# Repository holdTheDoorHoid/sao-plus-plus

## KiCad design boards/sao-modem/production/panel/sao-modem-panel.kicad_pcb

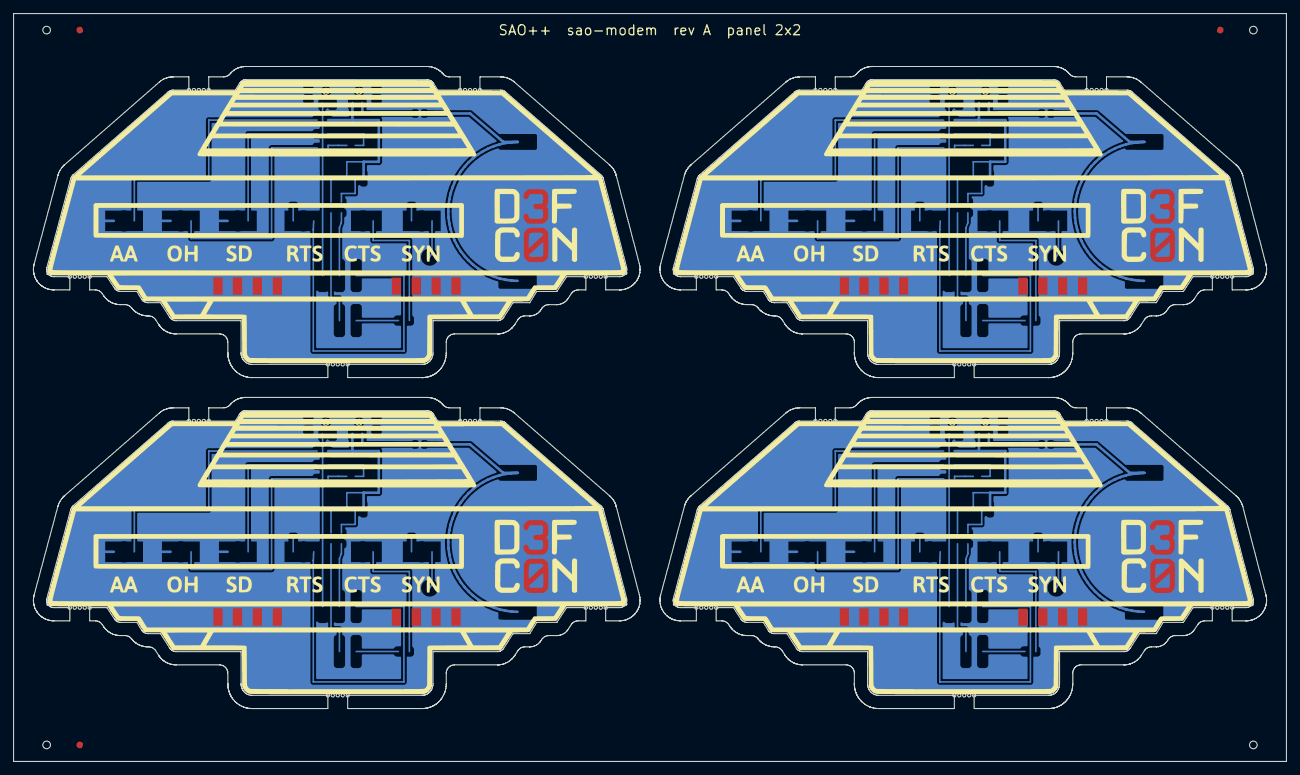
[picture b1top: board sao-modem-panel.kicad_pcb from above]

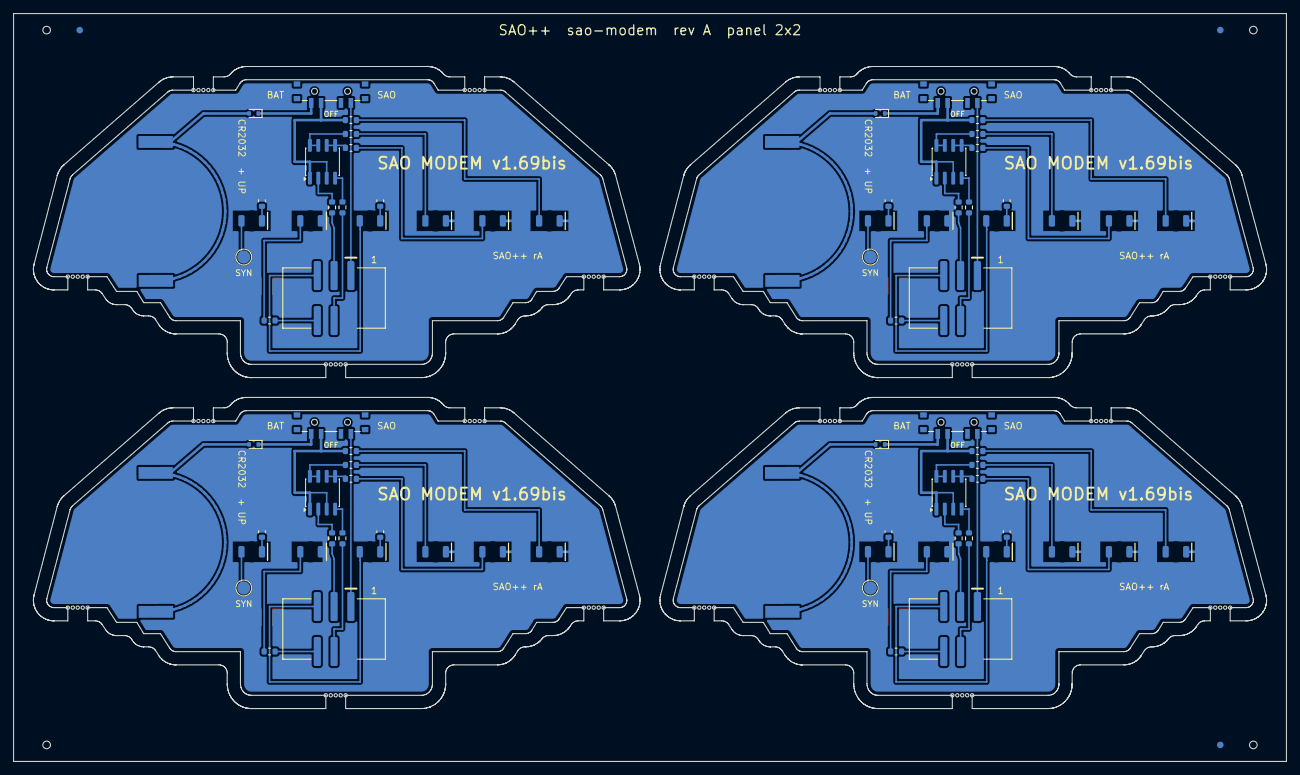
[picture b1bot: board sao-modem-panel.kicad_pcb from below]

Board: 2 copper layers, 192.4 x 113.1 mm, 80 parts (80 on the bottom side), 80 nets.

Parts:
BT101, BT201, BT301, BT401: CR2032; SAOPP_BAT-01_CR2032_SMD_TE_BAT-HLD-001
D101, D102, D103, D104, D105, D106, D201, D202, D203, D204, D205, D206, D301, D302, D303, D304, D305, D306, D401, D402, D403, D404, D405, D406: red; SAOPP_LED-10_1206_ReverseMount_ThroughBoard
D107, D207, D307, D407: RB751S40; D_SOD-523
J101, J201, J301, J401: SAO v1.69bis; SAOPP_CONN-01_BoxHeader_2x03_P2.54mm_SMD_XFCN_BH254VS-6P
Q101, Q201, Q301, Q401: DMP3085LSD; SOIC-8_3.9x4.9mm_P1.27mm
R101, R102, R103, R104, R105, R106, R201, R202, R203, R204, R205, R206, R301, R302, R303, R304, R305, R306, R401, R402, R403, R404, R405, R406: 1.3k; SAOPP_R_0603_1608Metric
R107, R207, R307, R407: 4.7k; R_0603_1608Metric
R108, R208, R308, R408: 10k; R_0603_1608Metric
SW101, SW201, SW301, SW401: SAO / OFF / BAT; SAOPP_SW-01_Slide_SP3T_CK_PCM13SMTR
TP1, TP1#2, TP1#3, TP1#4: SYN pad; TestPoint_Pad_D2.0mm

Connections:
AA_A: D101.2, R101.2
B2-AA_A: D201.2, R201.2
B2-CTS_A: D205.2, R205.1
B2-GND: BT201.2, D201.1, D202.1, D203.1, D205.1, J201.2, R204.2, R206.2
B2-GPIO1: D204.2, J201.5
B2-GPIO2: J201.6, R205.2
B2-G_SCL: Q201.4, R207.2
B2-G_SDA: Q201.2, R208.2
B2-OH_A: D202.2, R202.2
B2-Q_OH: Q201.5, Q201.6, R202.1
B2-Q_SD: Q201.7, Q201.8, R203.1
B2-RTS_K: D204.1, R204.1
B2-SCL: J201.4, R207.1
B2-SDA: J201.3, R208.1
B2-SD_A: D203.2, R203.2
B2-SYN: D206.2, TP1#3.1
B2-SYN_K: D206.1, R206.1
B2-VBAT: BT201.1, D207.2
B2-VCELL: D207.1, SW201.4
B2-VLOAD: Q201.1, Q201.3, R201.1, SW201.3
B2-VSAO: J201.1, SW201.1
B3-AA_A: D301.2, R301.2
B3-CTS_A: D305.2, R305.1
B3-GND: BT301.2, D301.1, D302.1, D303.1, D305.1, J301.2, R304.2, R306.2
B3-GPIO1: D304.2, J301.5
B3-GPIO2: J301.6, R305.2
B3-G_SCL: Q301.4, R307.2
B3-G_SDA: Q301.2, R308.2
B3-OH_A: D302.2, R302.2
B3-Q_OH: Q301.5, Q301.6, R302.1
B3-Q_SD: Q301.7, Q301.8, R303.1
B3-RTS_K: D304.1, R304.1
B3-SCL: J301.4, R307.1
B3-SDA: J301.3, R308.1
B3-SD_A: D303.2, R303.2
B3-SYN: D306.2, TP1#2.1
B3-SYN_K: D306.1, R306.1
B3-VBAT: BT301.1, D307.2
B3-VCELL: D307.1, SW301.4
B3-VLOAD: Q301.1, Q301.3, R301.1, SW301.3
B3-VSAO: J301.1, SW301.1
B4-AA_A: D401.2, R401.2
B4-CTS_A: D405.2, R405.1
B4-GND: BT401.2, D401.1, D402.1, D403.1, D405.1, J401.2, R404.2, R406.2
B4-GPIO1: D404.2, J401.5
B4-GPIO2: J401.6, R405.2
B4-G_SCL: Q401.4, R407.2
B4-G_SDA: Q401.2, R408.2
B4-OH_A: D402.2, R402.2
B4-Q_OH: Q401.5, Q401.6, R402.1
B4-Q_SD: Q401.7, Q401.8, R403.1
B4-RTS_K: D404.1, R404.1
B4-SCL: J401.4, R407.1
B4-SDA: J401.3, R408.1
B4-SD_A: D403.2, R403.2
B4-SYN: D406.2, TP1#4.1
B4-SYN_K: D406.1, R406.1
B4-VBAT: BT401.1, D407.2
B4-VCELL: D407.1, SW401.4
B4-VLOAD: Q401.1, Q401.3, R401.1, SW401.3
B4-VSAO: J401.1, SW401.1
CTS_A: D105.2, R105.1
GND: BT101.2, D101.1, D102.1, D103.1, D105.1, J101.2, R104.2, R106.2
GPIO1: D104.2, J101.5
GPIO2: J101.6, R105.2
G_SCL: Q101.4, R107.2
G_SDA: Q101.2, R108.2
OH_A: D102.2, R102.2
Q_OH: Q101.5, Q101.6, R102.1
Q_SD: Q101.7, Q101.8, R103.1
RTS_K: D104.1, R104.1
SCL: J101.4, R107.1
SDA: J101.3, R108.1
SD_A: D103.2, R103.2
SYN: D106.2, TP1.1
SYN_K: D106.1, R106.1
VBAT: BT101.1, D107.2
VCELL: D107.1, SW101.4
VLOAD: Q101.1, Q101.3, R101.1, SW101.3
VSAO: J101.1, SW101.1

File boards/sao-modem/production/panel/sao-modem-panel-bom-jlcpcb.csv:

Comment,Designator,Footprint,LCSC Part #
CR2032,"BT101,BT201,BT301,BT401",SAOPP_BAT-01_CR2032_SMD_TE_BAT-HLD-001,C7501066
red,"D101,D102,D103,D104,D105,D106,D201,D202,D203,D204,D205,D206,D301,D302,D303,D304,D305,D306,D401,D402,D403,D404,D405,D406",SAOPP_LED-10_1206_ReverseMount_ThroughBoard,C125107
RB751S40,"D107,D207,D307,D407",D_SOD-523,C232576
SAO v1.69bis,"J101,J201,J301,J401",SAOPP_CONN-01_BoxHeader_2x03_P2.54mm_SMD_XFCN_BH254VS-6P,C492445
DMP3085LSD,"Q101,Q201,Q301,Q401",SOIC-8_3.9x4.9mm_P1.27mm,
1.3k,"R101,R102,R103,R104,R105,R106,R201,R202,R203,R204,R205,R206,R301,R302,R303,R304,R305,R306,R401,R402,R403,R404,R405,R406",SAOPP_R_0603_1608Metric,C22767
4.7k,"R107,R207,R307,R407",R_0603_1608Metric,
10k,"R108,R208,R308,R408",R_0603_1608Metric,
SAO / OFF / BAT,"SW101,SW201,SW301,SW401",SAOPP_SW-01_Slide_SP3T_CK_PCM13SMTR,C221842

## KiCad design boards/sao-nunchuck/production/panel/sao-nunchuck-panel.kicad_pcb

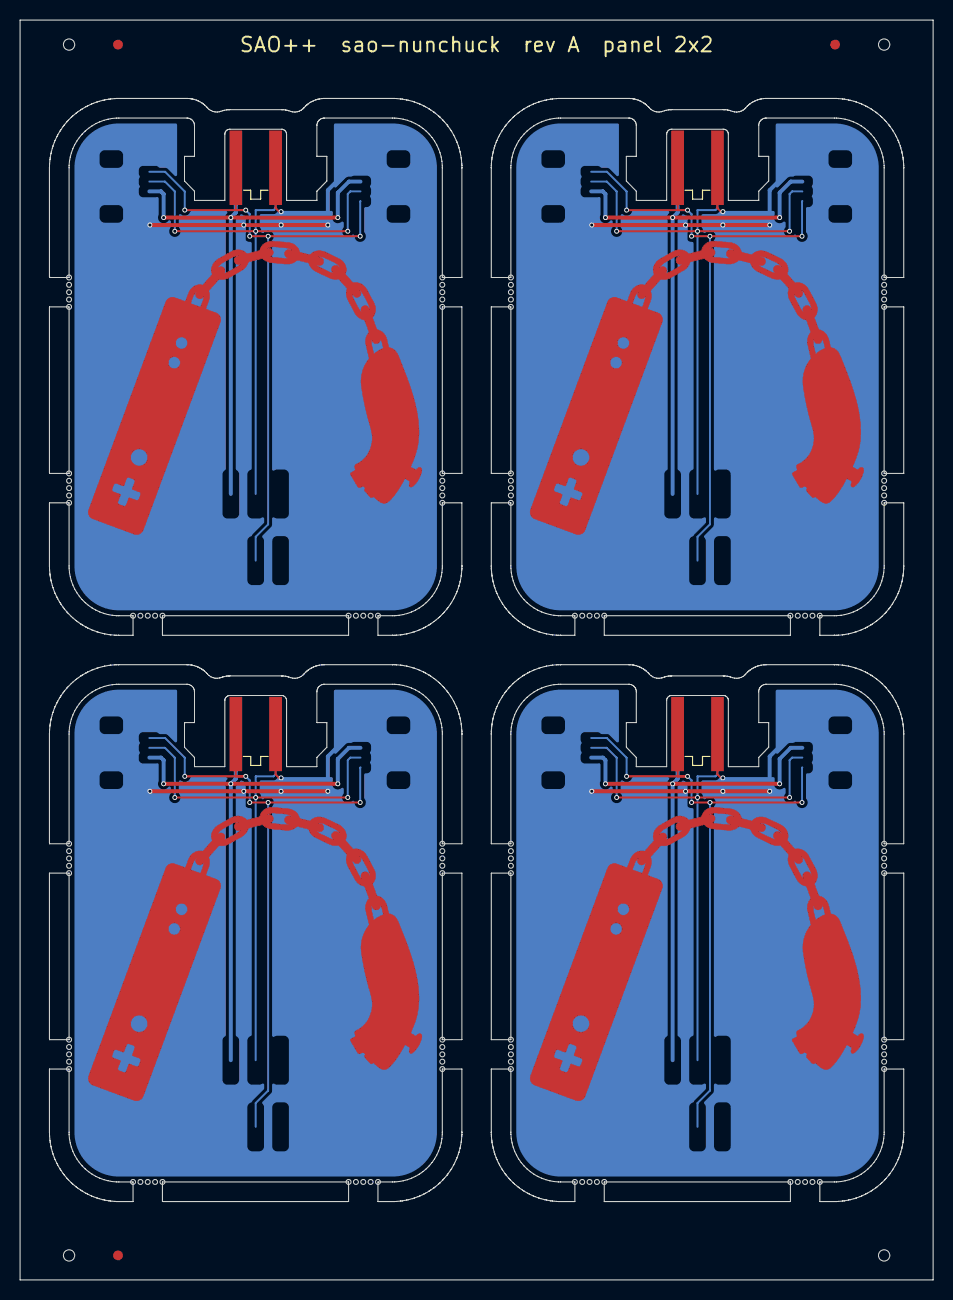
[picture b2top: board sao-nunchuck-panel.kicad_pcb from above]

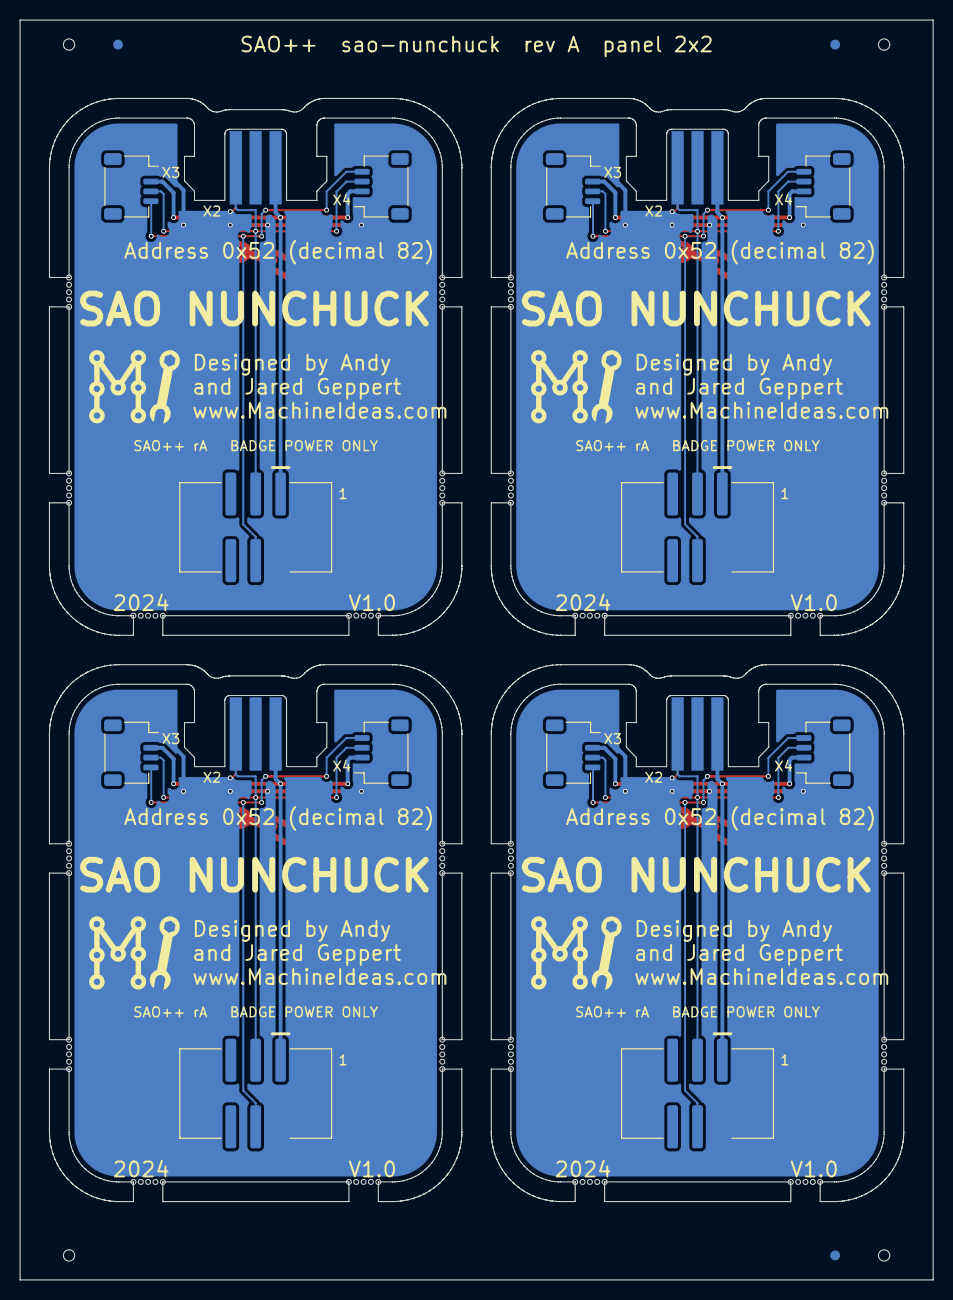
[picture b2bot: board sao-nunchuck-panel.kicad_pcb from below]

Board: 2 copper layers, 93.2 x 128.6 mm, 20 parts (16 on the bottom side), 16 nets.

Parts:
J101, J201, J301, J401: SAO v1.69bis; SAOPP_CONN-01_BoxHeader_2x03_P2.54mm_SMD_XFCN_BH254VS-6P
L1, L1#2, L1#3, L1#4: Machine_Ideas_logo
X102, X202, X302, X402: Nunchuck plug (board edge fingers); Nunchuck_Plug_EdgeFingers
X103, X104, X203, X204, X303, X304, X403, X404: Qwiic (pads only, not fitted); Qwiic_JST_SH_SM04B-SRSS-TB_NotFitted

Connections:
3V3: J101.1, X102.3, X103.2, X104.2
B2-3V3: J201.1, X202.3, X203.2, X204.2
B2-GND: J201.2, X202.6, X203.1, X204.1
B2-SCL: J201.4, X202.4, X203.4, X204.4
B2-SDA: J201.3, X202.1, X203.3, X204.3
B3-3V3: J301.1, X302.3, X303.2, X304.2
B3-GND: J301.2, X302.6, X303.1, X304.1
B3-SCL: J301.4, X302.4, X303.4, X304.4
B3-SDA: J301.3, X302.1, X303.3, X304.3
B4-3V3: J401.1, X402.3, X403.2, X404.2
B4-GND: J401.2, X402.6, X403.1, X404.1
B4-SCL: J401.4, X402.4, X403.4, X404.4
B4-SDA: J401.3, X402.1, X403.3, X404.3
GND: J101.2, X102.6, X103.1, X104.1
SCL: J101.4, X102.4, X103.4, X104.4
SDA: J101.3, X102.1, X103.3, X104.3

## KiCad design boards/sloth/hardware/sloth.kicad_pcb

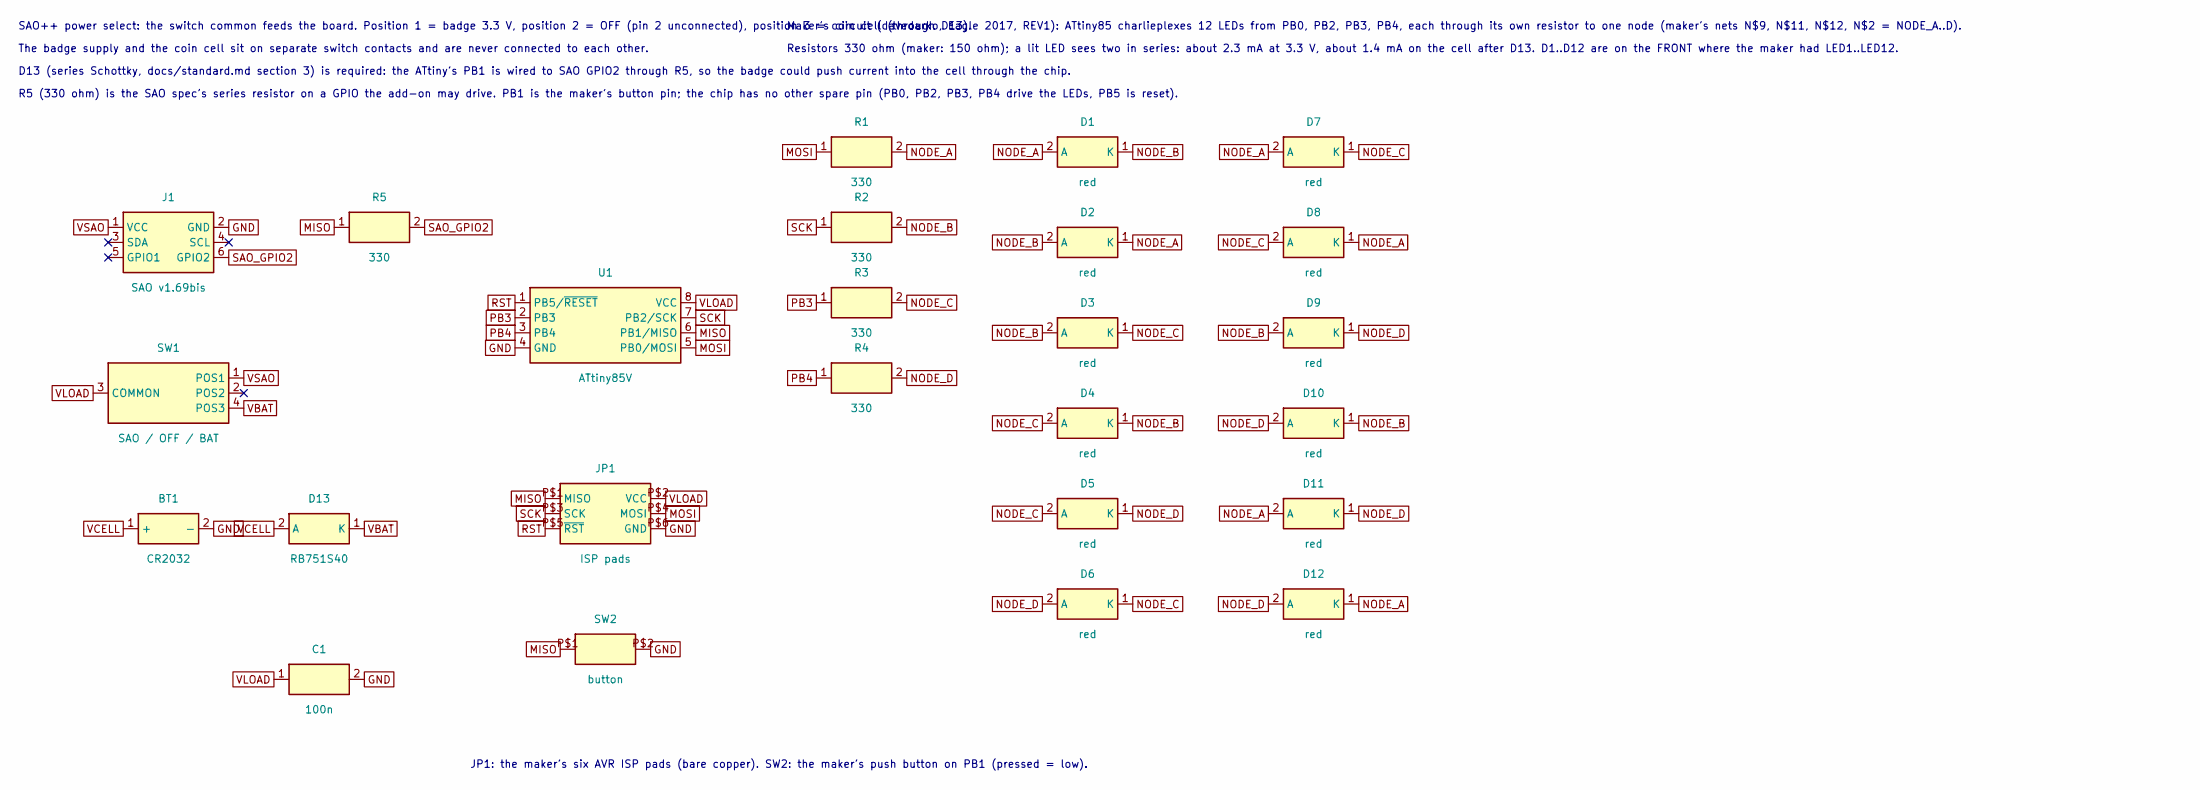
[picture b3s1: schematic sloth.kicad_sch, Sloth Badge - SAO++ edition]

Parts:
BT1: CR2032; SAOPP_BAT-01_CR2032_SMD_TE_BAT-HLD-001; MPN BAT-HLD-001; LCSC C7501066
C1: 100n; SAOPP_C_0603_1608Metric; MPN CC0603KRX7R9BB104; LCSC C14663
D1, D2, D3, D4, D5, D6, D7, D8, D9, D10, D11, D12: red; LED_0603_1608Metric_Pad1.05x0.95mm_HandSolder; MPN LTST-C191KRKT; LCSC C125099
D13: RB751S40; D_SOD-523; MPN RB751S40T1G; LCSC C232576
J1: SAO v1.69bis; SAOPP_CONN-01_BoxHeader_2x03_P2.54mm_SMD_XFCN_BH254VS-6P; MPN BH254VS-6P; LCSC C492445
JP1: ISP pads; 2X3_SMD_PAD; MPN none: bare pads, nothing fitted
R1, R2, R3, R4, R5: 330; SAOPP_R_0603_1608Metric; MPN 0603WAF3300T5E; LCSC C23138
SW1: SAO / OFF / BAT; SAOPP_SW-01_Slide_SP3T_CK_PCM13SMTR; MPN PCM13SMTR; LCSC C221842
SW2: button; TACTILE-SWITCH-1101NE; MPN SparkFun COM-08229 class (6 x 3.5 mm, 2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
U1: ATtiny85V; SO08-EIAJ; MPN ATTINY85V-10SU; LCSC C152192

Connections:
GND: BT1.2 (-), C1.2, J1.2 (GND), JP1.P$6 (GND), SW2.P$2, U1.4 (GND)
MISO: JP1.P$1 (MISO), R5.1, SW2.P$1, U1.6 (PB1/MISO)
MOSI: JP1.P$4 (MOSI), R1.1, U1.5 (PB0/MOSI)
NODE_A: D1.2 (A), D2.1 (K), D7.2 (A), D8.1 (K), D11.2 (A), D12.1 (K), R1.2
NODE_B: D1.1 (K), D2.2 (A), D3.2 (A), D4.1 (K), D9.2 (A), D10.1 (K), R2.2
NODE_C: D3.1 (K), D4.2 (A), D5.2 (A), D6.1 (K), D7.1 (K), D8.2 (A), R3.2
NODE_D: D5.1 (K), D6.2 (A), D9.1 (K), D10.2 (A), D11.1 (K), D12.2 (A), R4.2
PB3: R3.1, U1.2 (PB3)
PB4: R4.1, U1.3 (PB4)
RST: JP1.P$5 (~RST), U1.1 (PB5/~RESET)
SAO_GPIO2: J1.6 (GPIO2), R5.2
SCK: JP1.P$3 (SCK), R2.1, U1.7 (PB2/SCK)
VBAT: D13.1 (K), SW1.4 (POS3)
VCELL: BT1.1 (+), D13.2 (A)
VLOAD: C1.1, JP1.P$2 (VCC), SW1.3 (COMMON), U1.8 (VCC)
VSAO: J1.1 (VCC), SW1.1 (POS1)

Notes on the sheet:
SAO++ power select: the switch common feeds the board. Position 1 = badge 3.3 V, position 2 = OFF (pin 2 unconnected), position 3 = coin cell (through D13).
The badge supply and the coin cell sit on separate switch contacts and are never connected to each other.
D13 (series Schottky, docs/standard.md section 3) is required: the ATtiny's PB1 is wired to SAO GPIO2 through R5, so the badge could push current into the cell through the chip.
R5 (330 ohm) is the SAO spec's series resistor on a GPIO the add-on may drive. PB1 is the maker's button pin; the chip has no other spare pin (PB0, PB2, PB3, PB4 drive the LEDs, PB5 is reset).
Maker's circuit (davedarko, Eagle 2017, REV1): ATtiny85 charlieplexes 12 LEDs from PB0, PB2, PB3, PB4, each through its own resistor to one node (maker's nets N$9, N$11, N$12, N$2 = NODE_A..D).
Resistors 330 ohm (maker: 150 ohm); a lit LED sees two in series: about 2.3 mA at 3.3 V, about 1.4 mA on the cell after D13. D1..D12 are on the FRONT where the maker had LED1..LED12.
JP1: the maker's six AVR ISP pads (bare copper). SW2: the maker's push button on PB1 (pressed = low).

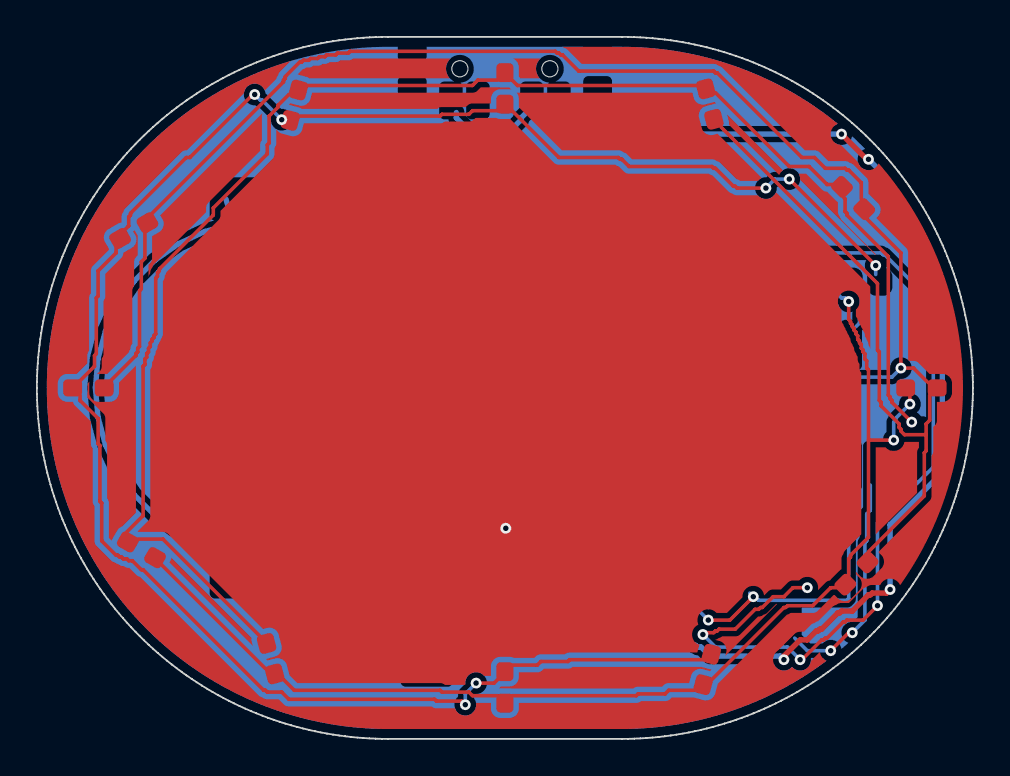
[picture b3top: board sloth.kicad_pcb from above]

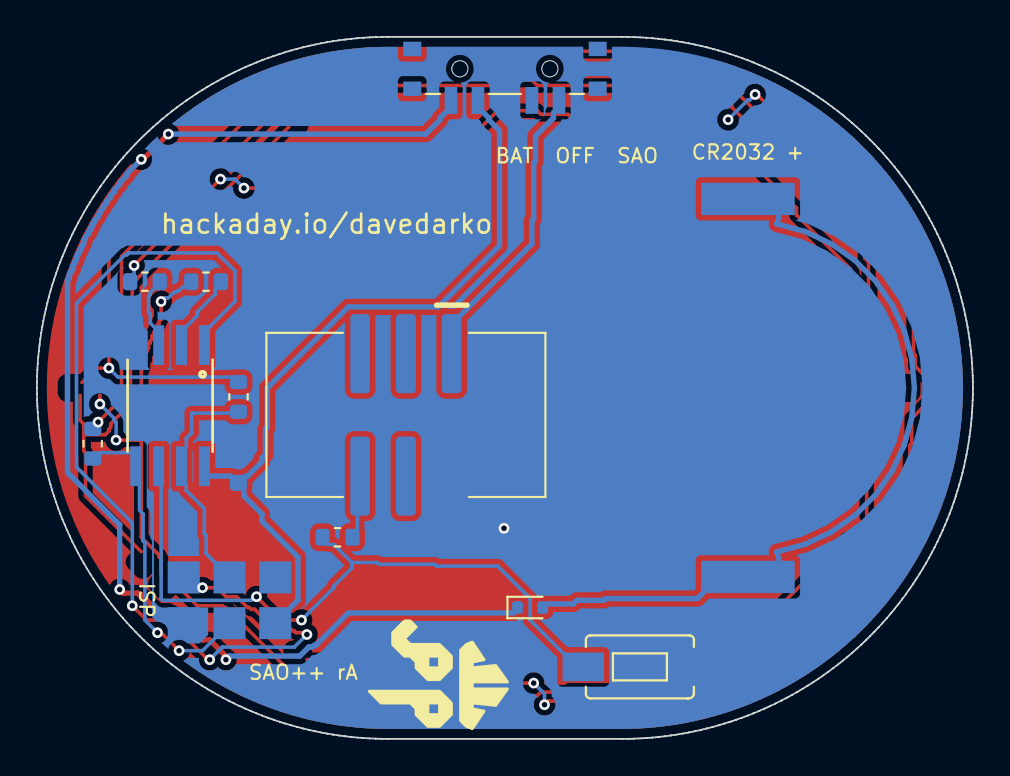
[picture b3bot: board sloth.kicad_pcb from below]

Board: 2 copper layers, 52.0 x 39.0 mm, 25 parts (13 on the bottom side), 16 nets.

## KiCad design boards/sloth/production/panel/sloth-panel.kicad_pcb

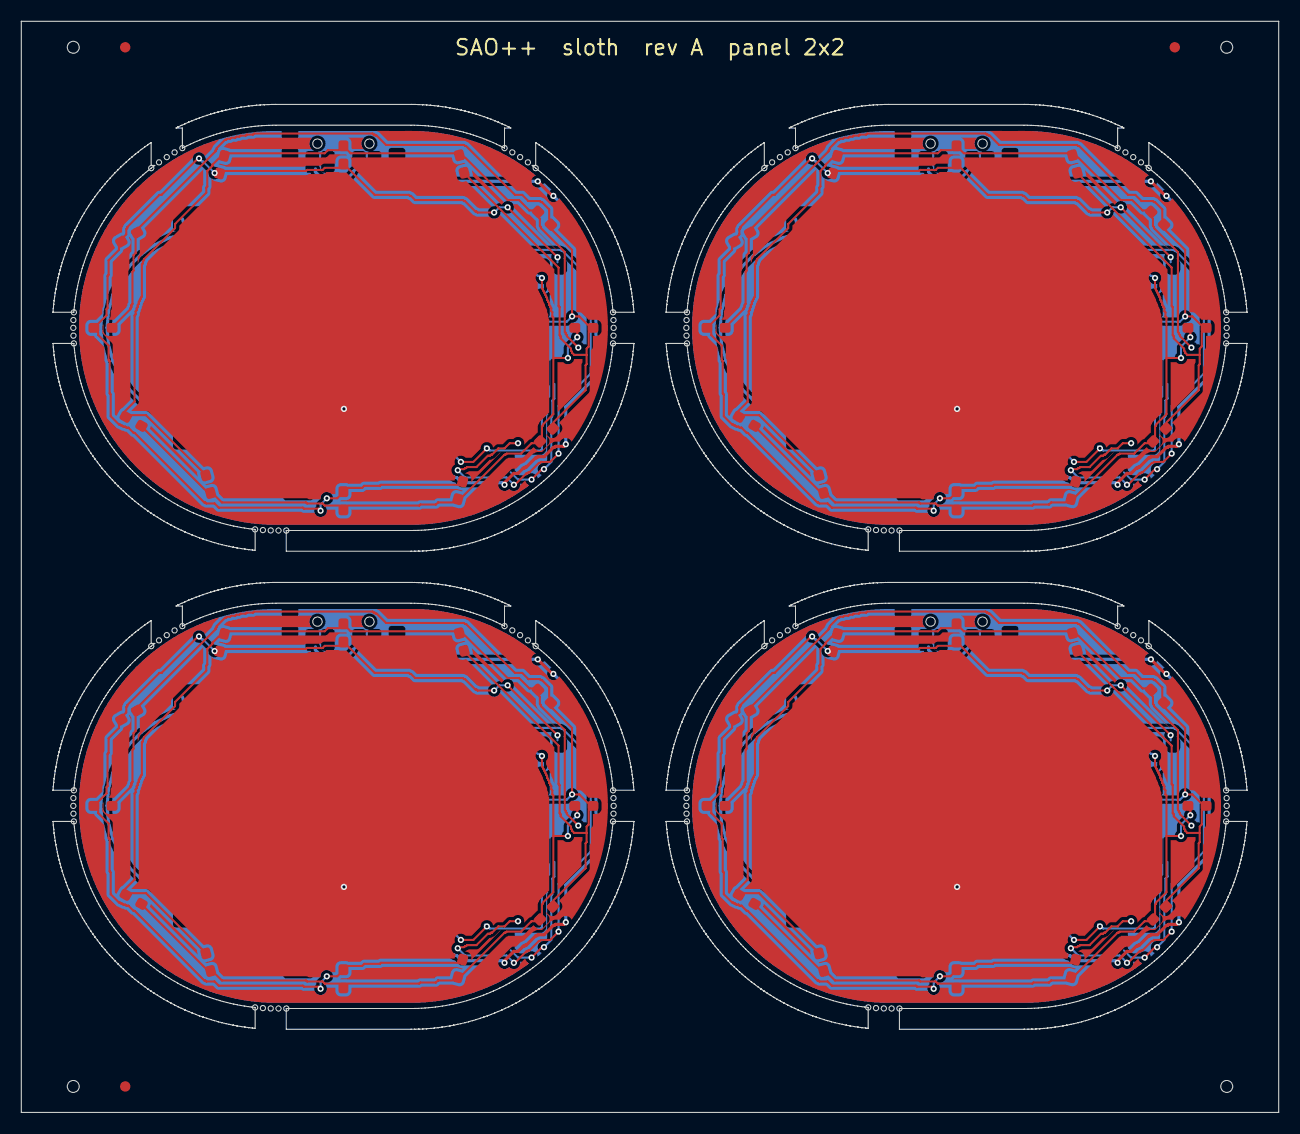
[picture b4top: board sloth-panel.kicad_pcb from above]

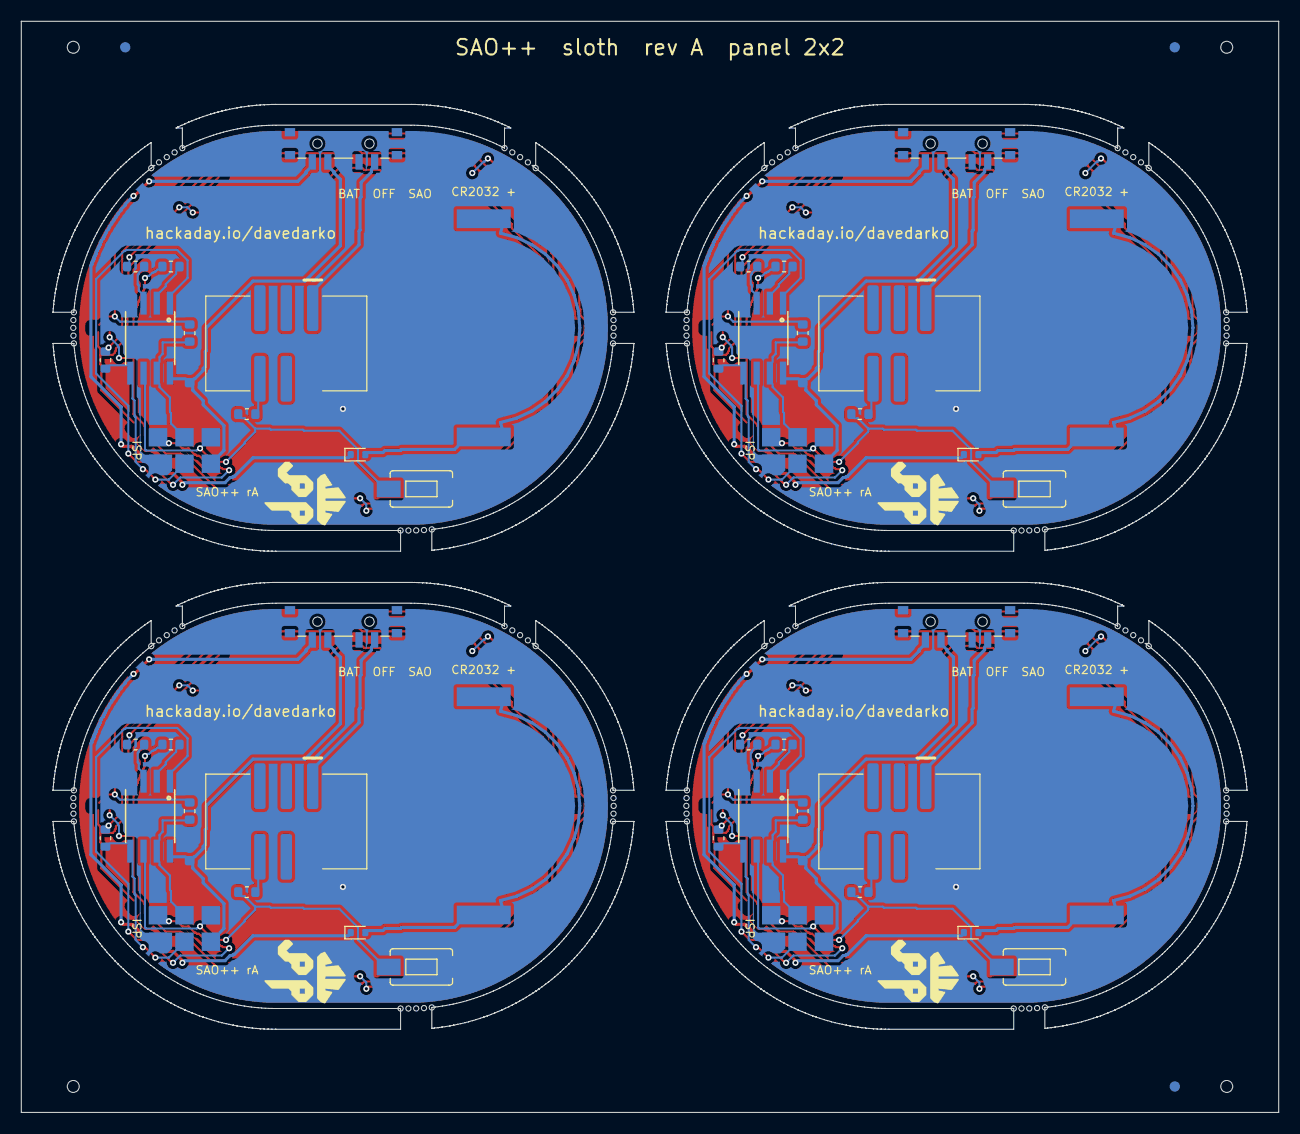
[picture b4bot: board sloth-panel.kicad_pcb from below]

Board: 2 copper layers, 121.0 x 105.0 mm, 100 parts (52 on the bottom side), 64 nets.

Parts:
BT101, BT201, BT301, BT401: CR2032; SAOPP_BAT-01_CR2032_SMD_TE_BAT-HLD-001
C101, C201, C301, C401: 100n; SAOPP_C_0603_1608Metric
D101, D102, D103, D104, D105, D106, D107, D108, D109, D110, D111, D112, D201, D202, D203, D204, D205, D206, D207, D208, D209, D210, D211, D212, D301, D302, D303, D304, D305, D306, D307, D308, D309, D310, D311, D312, D401, D402, D403, D404, D405, D406, D407, D408, D409, D410, D411, D412: red; LED_0603_1608Metric_Pad1.05x0.95mm_HandSolder
D113, D213, D313, D413: RB751S40; D_SOD-523
J101, J201, J301, J401: SAO v1.69bis; SAOPP_CONN-01_BoxHeader_2x03_P2.54mm_SMD_XFCN_BH254VS-6P
JP101, JP201, JP301, JP401: ISP pads; 2X3_SMD_PAD
R101, R102, R103, R104, R105, R201, R202, R203, R204, R205, R301, R302, R303, R304, R305, R401, R402, R403, R404, R405: 330; SAOPP_R_0603_1608Metric
SW101, SW201, SW301, SW401: SAO / OFF / BAT; SAOPP_SW-01_Slide_SP3T_CK_PCM13SMTR
SW102, SW202, SW302, SW402: button; TACTILE-SWITCH-1101NE
U101, U201, U301, U401: ATtiny85V; SO08-EIAJ

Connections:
B2-GND: BT201.2, C201.2, J201.2, JP201.P$6, SW202.P$2, U201.4
B2-MISO: JP201.P$1, R205.1, SW202.P$1, U201.6
B2-MOSI: JP201.P$4, R201.1, U201.5
B2-NODE_A: D201.2, D202.1, D207.2, D208.1, D211.2, D212.1, R201.2
B2-NODE_B: D201.1, D202.2, D203.2, D204.1, D209.2, D210.1, R202.2
B2-NODE_C: D203.1, D204.2, D205.2, D206.1, D207.1, D208.2, R203.2
B2-NODE_D: D205.1, D206.2, D209.1, D210.2, D211.1, D212.2, R204.2
B2-PB3: R203.1, U201.2
B2-PB4: R204.1, U201.3
B2-RST: JP201.P$5, U201.1
B2-SAO_GPIO2: J201.6, R205.2
B2-SCK: JP201.P$3, R202.1, U201.7
B2-VBAT: D213.1, SW201.4
B2-VCELL: BT201.1, D213.2
B2-VLOAD: C201.1, JP201.P$2, SW201.3, U201.8
B2-VSAO: J201.1, SW201.1
B3-GND: BT301.2, C301.2, J301.2, JP301.P$6, SW302.P$2, U301.4
B3-MISO: JP301.P$1, R305.1, SW302.P$1, U301.6
B3-MOSI: JP301.P$4, R301.1, U301.5
B3-NODE_A: D301.2, D302.1, D307.2, D308.1, D311.2, D312.1, R301.2
B3-NODE_B: D301.1, D302.2, D303.2, D304.1, D309.2, D310.1, R302.2
B3-NODE_C: D303.1, D304.2, D305.2, D306.1, D307.1, D308.2, R303.2
B3-NODE_D: D305.1, D306.2, D309.1, D310.2, D311.1, D312.2, R304.2
B3-PB3: R303.1, U301.2
B3-PB4: R304.1, U301.3
B3-RST: JP301.P$5, U301.1
B3-SAO_GPIO2: J301.6, R305.2
B3-SCK: JP301.P$3, R302.1, U301.7
B3-VBAT: D313.1, SW301.4
B3-VCELL: BT301.1, D313.2
B3-VLOAD: C301.1, JP301.P$2, SW301.3, U301.8
B3-VSAO: J301.1, SW301.1
B4-GND: BT401.2, C401.2, J401.2, JP401.P$6, SW402.P$2, U401.4
B4-MISO: JP401.P$1, R405.1, SW402.P$1, U401.6
B4-MOSI: JP401.P$4, R401.1, U401.5
B4-NODE_A: D401.2, D402.1, D407.2, D408.1, D411.2, D412.1, R401.2
B4-NODE_B: D401.1, D402.2, D403.2, D404.1, D409.2, D410.1, R402.2
B4-NODE_C: D403.1, D404.2, D405.2, D406.1, D407.1, D408.2, R403.2
B4-NODE_D: D405.1, D406.2, D409.1, D410.2, D411.1, D412.2, R404.2
B4-PB3: R403.1, U401.2
B4-PB4: R404.1, U401.3
B4-RST: JP401.P$5, U401.1
B4-SAO_GPIO2: J401.6, R405.2
B4-SCK: JP401.P$3, R402.1, U401.7
B4-VBAT: D413.1, SW401.4
B4-VCELL: BT401.1, D413.2
B4-VLOAD: C401.1, JP401.P$2, SW401.3, U401.8
B4-VSAO: J401.1, SW401.1
GND: BT101.2, C101.2, J101.2, JP101.P$6, SW102.P$2, U101.4
MISO: JP101.P$1, R105.1, SW102.P$1, U101.6
MOSI: JP101.P$4, R101.1, U101.5
NODE_A: D101.2, D102.1, D107.2, D108.1, D111.2, D112.1, R101.2
NODE_B: D101.1, D102.2, D103.2, D104.1, D109.2, D110.1, R102.2
NODE_C: D103.1, D104.2, D105.2, D106.1, D107.1, D108.2, R103.2
NODE_D: D105.1, D106.2, D109.1, D110.2, D111.1, D112.2, R104.2
PB3: R103.1, U101.2
PB4: R104.1, U101.3
RST: JP101.P$5, U101.1
SAO_GPIO2: J101.6, R105.2
SCK: JP101.P$3, R102.1, U101.7
VBAT: D113.1, SW101.4
VCELL: BT101.1, D113.2
VLOAD: C101.1, JP101.P$2, SW101.3, U101.8
VSAO: J101.1, SW101.1

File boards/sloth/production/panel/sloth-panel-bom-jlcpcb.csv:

Comment,Designator,Footprint,LCSC Part #
CR2032,"BT101,BT201,BT301,BT401",SAOPP_BAT-01_CR2032_SMD_TE_BAT-HLD-001,C7501066
100n,"C101,C201,C301,C401",SAOPP_C_0603_1608Metric,C14663
red,"D101,D102,D103,D104,D105,D106,D107,D108,D109,D110,D111,D112,D201,D202,D203,D204,D205,D206,D207,D208,D209,D210,D211,D212,D301,D302,D303,D304,D305,D306,D307,D308,D309,D310,D311,D312,D401,D402,D403,D404,D405,D406,D407,D408,D409,D410,D411,D412",LED_0603_1608Metric_Pad1.05x0.95mm_HandSolder,C125099
RB751S40,"D113,D213,D313,D413",D_SOD-523,C232576
SAO v1.69bis,"J101,J201,J301,J401",SAOPP_CONN-01_BoxHeader_2x03_P2.54mm_SMD_XFCN_BH254VS-6P,C492445
ISP pads,"JP101,JP201,JP301,JP401",2X3_SMD_PAD,
330,"R101,R102,R103,R104,R105,R201,R202,R203,R204,R205,R301,R302,R303,R304,R305,R401,R402,R403,R404,R405",SAOPP_R_0603_1608Metric,C23138
SAO / OFF / BAT,"SW101,SW201,SW301,SW401",SAOPP_SW-01_Slide_SP3T_CK_PCM13SMTR,C221842
button,"SW102,SW202,SW302,SW402",TACTILE-SWITCH-1101NE,
ATtiny85V,"U101,U201,U301,U401",SO08-EIAJ,C152192

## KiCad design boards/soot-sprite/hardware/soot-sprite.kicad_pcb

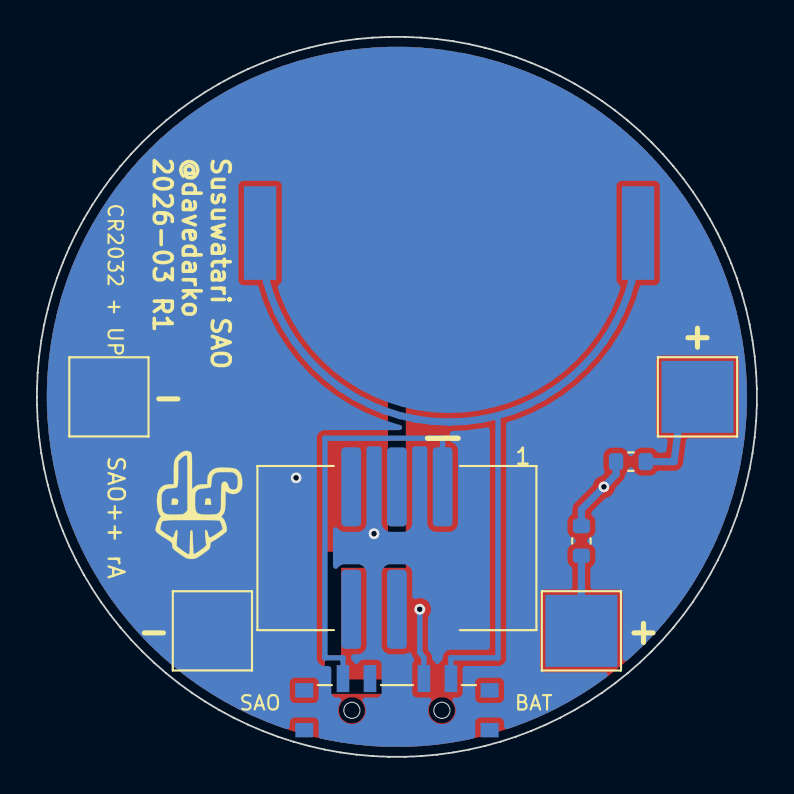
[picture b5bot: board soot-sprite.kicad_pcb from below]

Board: 2 copper layers, 40.0 x 40.0 mm, 10 parts (10 on the bottom side), 6 nets.

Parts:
BT1: CR2032; SAOPP_BAT-01_CR2032_SMD_TE_BAT-HLD-001
J1: SAO v1.69bis; SAOPP_CONN-01_BoxHeader_2x03_P2.54mm_SMD_XFCN_BH254VS-6P
R1, R2: 1.3k; SAOPP_R_0603_1608Metric
Ref**: Val**; davedarko_logo_silk_outline
SW1: SAO / OFF / BAT; SAOPP_SW-01_Slide_SP3T_CK_PCM13SMTR
TP1, TP2, TP3, TP4: LED leg pad; TestPoint_Pad_4.0x4.0mm

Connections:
ARM_A: R1.2, TP4.1
GND: BT1.2, J1.2, TP1.1, TP2.1
LEG_A: R2.2, TP3.1
VBAT: BT1.1, SW1.4
VLOAD: R1.1, R2.1, SW1.3
VSAO: J1.1, SW1.1

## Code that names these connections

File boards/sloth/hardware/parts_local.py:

"""Parts the Sloth needs that the shared SAO++ library does not have (yet). Read by tools/saopp_symbols.load_local.

All five are Knight Rider's already-verified local parts (boards/knight-rider/hardware/parts_local.py), copied with
their symbol entries unchanged except the footprint library name; footprints copied by make_local_footprints.py.
Format as in tools/saopp_symbols.py:
  name: (ref prefix, value, footprint, fields, half-width, [(pin number, pin name, side, row), ...])
"""
LOCAL_SYMBOLS = {
    # the maker's chip: ATtiny85 in the 208 mil (EIAJ) SOIC-8. The low-voltage "V" grade (1.8-5.5 V) because on the coin
    # cell the chip sees about 2.7 V after the cell diode, which is the bottom of the standard -20 grade's range
    "ATtiny85_SOIC8_EIAJ": ("U", "ATtiny85V", "sloth-local:SO08-EIAJ",
                            {"SAOPP_ID": "", "MPN": "ATTINY85V-10SU", "LCSC": "C152192"}, 5,
                            [("1", "PB5/~{RESET}", "L", 0), ("2", "PB3", "L", 1), ("3", "PB4", "L", 2), ("4", "GND", "L", 3),
                             ("8", "VCC", "R", 0), ("7", "PB2/SCK", "R", 1), ("6", "PB1/MISO", "R", 2), ("5", "PB0/MOSI", "R", 3)]),
    # forward-facing red LED, on the FRONT (art side) in the maker's ring of twelve round the sloth's face
    "LED_0603_Red_Front": ("D", "red", "sloth-local:LED_0603_1608Metric_Pad1.05x0.95mm_HandSolder",
                           {"SAOPP_ID": "", "MPN": "LTST-C191KRKT", "LCSC": "C125099"}, 2,
                           [("2", "A", "L", 0), ("1", "K", "R", 0)]),
    # the maker's push button (on PB1/MISO, as on his board); 6 x 3.5 mm two-pad SMD tactile switch
    "Button_SMD_6x3.5": ("SW", "button", "sloth-local:TACTILE-SWITCH-1101NE",
                         {"SAOPP_ID": "", "MPN": "SparkFun COM-08229 class (6 x 3.5 mm, 2 pads at 6.3 mm)", "LCSC": ""}, 2,
                         [("P$1", "~", "L", 0), ("P$2", "~", "R", 0)]),
    # the maker's six AVR ISP programming pads (bare copper, nothing fitted); standard AVR 6-pin ISP order
    "ISP_Pads_AVR_2x3": ("JP", "ISP pads", "sloth-local:2X3_SMD_PAD",
                         {"SAOPP_ID": "", "MPN": "none: bare pads, nothing fitted", "LCSC": ""}, 3,
                         [("P$1", "MISO", "L", 0), ("P$3", "SCK", "L", 1), ("P$5", "~{RST}", "L", 2),
                          ("P$2", "VCC", "R", 0), ("P$4", "MOSI", "R", 1), ("P$6", "GND", "R", 2)]),
    # the series cell diode docs/standard.md section 3 requires (this board wires the ATtiny's PB1 to SAO GPIO2)
    "D_Schottky_Cell": ("D", "RB751S40", "sloth-local:D_SOD-523",
                        {"SAOPP_ID": "SAOPP-D-01", "MPN": "RB751S40T1G", "LCSC": "C232576"}, 2,
                        [("2", "A", "L", 0), ("1", "K", "R", 0)]),
}

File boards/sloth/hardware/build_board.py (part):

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D13_C = (124.6, 131.7)
d13 = place("D13", D13_C, ("2", (D13_C[0] - 0.7, D13_C[1])))         # beside the clip's lower + pad: anode (cell) left, cathode right
res = {}
# each LED resistor beside the chip pin that drives it: PB3 / PB4 (top row) above the chip, SCK to its left, MOSI to its
# right; the space between the chip and the ISP pads stays clear for the four programming lines
for ref, (x, y) in {"R3": (142.6, 113.6), "R4": (146.0, 113.6)}.items():
    res[ref] = place(ref, (x, y), ("1", (x - 0.825, y)))              # pad 1 (chip side) left
res["R2"] = place("R2", (140.8, 120.0), ("1", (140.8, 120.0 + 0.825)))  # pad 1 (SCK) down
res["R1"] = place("R1", (148.9, 122.6), ("1", (148.9, 122.6 + 0.825)))  # pad 1 (MOSI) down
res["R5"] = place("R5", (135.3, 127.8), ("1", (135.3 + 0.825, 127.8)))  # MISO right, badge GPIO2 left

_pad_ok = grown(body, -0.25)
for fp in board.GetFootprints():
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    if not ok:
        raise SystemExit(f"routing failed: {net}")
# 2. the back: a few net orders are tried in turn (bounded by the router's 5-minute cap); the first that routes wins.
#    Two supplies are fenced (FENCE): VLOAD may not ring the chip's top pins, and the cell feed VBAT goes round the outside.
#    The first order routes today; the others are kept as fall-backs if a part is moved. Ground is not routed (see below).
SNAP = g.owner.copy()
FENCE = {
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}
SUPPLY = ["VCELL", "VSAO", "VLOAD"]
TRIES = [
    SUPPLY + ["PB3", "PB4", "SCK", "MISO", "MOSI", "RST", "SAO_GPIO2", "VBAT"],
    SUPPLY + ["SCK", "MISO", "MOSI", "RST", "PB3", "PB4", "SAO_GPIO2", "VBAT"],
    SUPPLY + ["SCK", "MISO", "RST", "MOSI", "PB3", "PB4", "SAO_GPIO2", "VBAT"],
    SUPPLY + ["MISO", "SCK", "MOSI", "PB3", "PB4", "RST", "SAO_GPIO2", "VBAT"],
]
if os.environ.get("SLOTH_ORDER"):                         # debugging aid: try one given order of the back nets
    TRIES = [SUPPLY + os.environ["SLOTH_ORDER"].split(",")]
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

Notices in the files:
boards/sao-modem/production/panel/sao-modem-panel.kicad_pcb:
Original design: hamster (@hamster), SAO Modem 1.69bis, DEF CON 30, MIT license, github.com/hamster/defcon30
boards/sao-nunchuck/production/panel/sao-nunchuck-panel.kicad_pcb:
Original design: Andy and Jared Geppert (ageppert), SAO Nunchuck V1.0, 2024, MIT license, github.com/ageppert/SAO_Nunchuck
